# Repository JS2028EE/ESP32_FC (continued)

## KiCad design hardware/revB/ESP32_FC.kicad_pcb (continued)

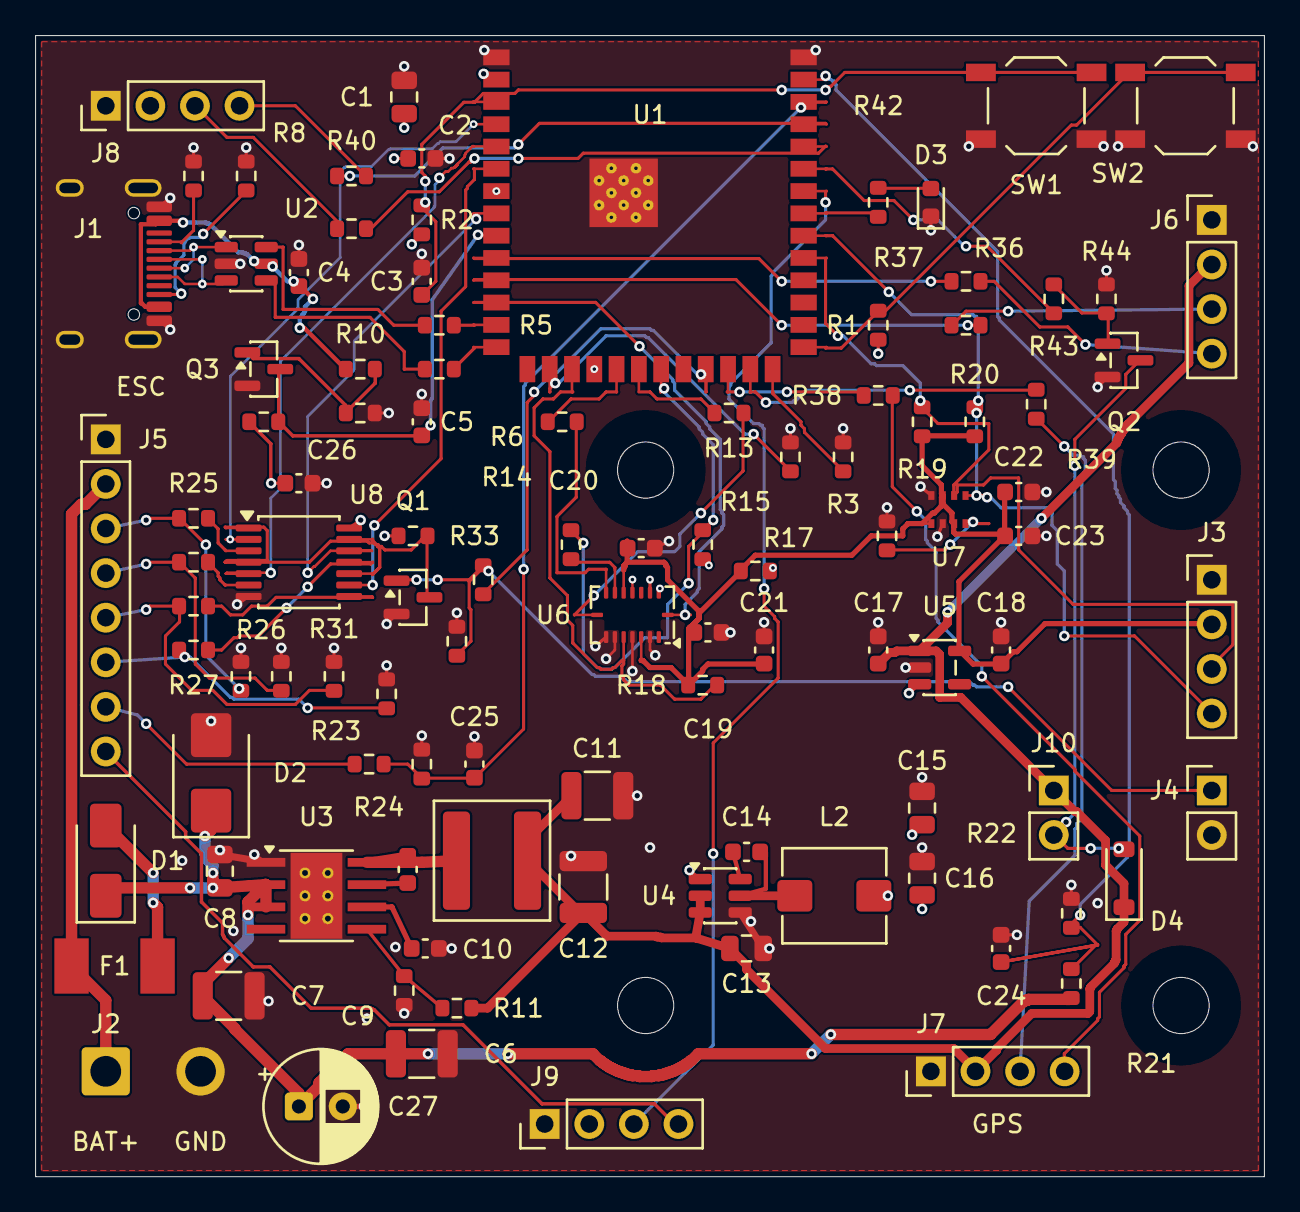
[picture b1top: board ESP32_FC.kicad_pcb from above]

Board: 4 copper layers, 70.0 x 65.0 mm, 107 parts (0 on the bottom side), 79 nets.

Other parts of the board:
H1, H2, H3, H4: MountingHole_3.2mm_M3

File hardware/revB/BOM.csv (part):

Reference,Value,MPN,Footprint,Specification,Sheet
C1,22u,GRM21BR61C226ME44L,Capacitor_SMD:C_0805_2012Metric,"X5R 16V 20%, 0805; board operation <=85C",ESP32_FC
C2,100n,GRM188R71C104KA01D,Capacitor_SMD:C_0603_1608Metric,"X7R, 16V",ESP32_FC
C3,1u,GRM188R71C105KA12D,Capacitor_SMD:C_0603_1608Metric,"X7R, 16V",ESP32_FC
C4,100n,GRM188R71C104KA01D,Capacitor_SMD:C_0603_1608Metric,"X7R, 16V",ESP32_FC
C5,10n,GRM188R71H103KA01D,Capacitor_SMD:C_0603_1608Metric,"X7R, 16V",ESP32_FC
J1,USB-C / USB2 FS,TYPE-C-31-M-12,FC_Prototype:USB_C_HRO_Edge,"['name', 'Specification']",ESP32_FC
Q3,DMN2056U,DMN2056U-7,Package_TO_SOT_SMD:SOT-23,VBUS detector; drain isolated from USB supply when MCU is unpowered,ESP32_FC
R1,10k,RC0603FR-0710KL,Resistor_SMD:R_0603_1608Metric,"1%, 0.1W",ESP32_FC
R2,10k,RC0603FR-0710KL,Resistor_SMD:R_0603_1608Metric,"1%, 0.1W",ESP32_FC
R3,10k,RC0603FR-0710KL,Resistor_SMD:R_0603_1608Metric,"1%, 0.1W",ESP32_FC
R4,10k,RC0603FR-0710KL,Resistor_SMD:R_0603_1608Metric,"1%, 0.1W",ESP32_FC
R5,22R,RC0603FR-0722RL,Resistor_SMD:R_0603_1608Metric,"1%, 0.1W",ESP32_FC
R6,22R,RC0603FR-0722RL,Resistor_SMD:R_0603_1608Metric,"1%, 0.1W",ESP32_FC
R7,5.1k,RC0603FR-075K1L,Resistor_SMD:R_0603_1608Metric,"1%, 0.1W",ESP32_FC
R8,5.1k,RC0603FR-075K1L,Resistor_SMD:R_0603_1608Metric,"1%, 0.1W",ESP32_FC
R9,10k,RC0603FR-0710KL,Resistor_SMD:R_0603_1608Metric,"1%, 0.1W",ESP32_FC
R10,100k,RC0603FR-07100KL,Resistor_SMD:R_0603_1608Metric,"1%, 0.1W",ESP32_FC
R46,10k,RC0603FR-0710KL,Resistor_SMD:R_0603_1608Metric,"1%, 0.1W; active-low VBUS sense pull-up",ESP32_FC
SW1,RESET,TL3342F160QG,Button_Switch_SMD:SW_SPST_TL3342,"['name', 'Specification']",ESP32_FC
SW2,BOOT,TL3342F160QG,Button_Switch_SMD:SW_SPST_TL3342,"['name', 'Specification']",ESP32_FC
U1,ESP32-S3-WROOM-1-N8R8,ESP32-S3-WROOM-1-N8R8,FC_Prototype:ESP32_S3_WROOM_Edge,8MB flash / 8MB octal PSRAM; GPIO35/36/37 unavailable,ESP32_FC
U2,USBLC6-2SC6,USBLC6-2SC6,Package_TO_SOT_SMD:SOT-23-6,"['name', 'Specification']",ESP32_FC
C6,2.2u / 100V,GRM32ER72A225KA35L,Capacitor_SMD:C_1210_3225Metric,Murata 1210 X7R 100V 10%; ceramic bypass plus C27 bulk damping,Power
C7,2.2u / 100V,GRM32ER72A225KA35L,Capacitor_SMD:C_1210_3225Metric,Murata 1210 X7R 100V 10%; local input bypass,Power
C8,220n / 100V,C0805C224K1RACTU,Capacitor_SMD:C_0805_2012Metric,X7R 100V directly at VIN-PGND,Power
C9,1u / 16V,GRM188R71C105KA12D,Capacitor_SMD:C_0603_1608Metric,"X7R, 16V",Power
C10,100n,GRM188R71C104KA01D,Capacitor_SMD:C_0603_1608Metric,"X7R, 16V",Power
C11,22u / 25V,GRM32ER71E226KE15L,Capacitor_SMD:C_1210_3225Metric,"X7R 25V 10%, 1210; both output capacitors required; DC-bias/temperature derating applies",Power
C12,22u / 25V,GRM32ER71E226KE15L,Capacitor_SMD:C_1210_3225Metric,"X7R 25V 10%, 1210; both output capacitors required; DC-bias/temperature derating applies",Power
C13,22u,GRM21BR61C226ME44L,Capacitor_SMD:C_0805_2012Metric,"X5R 16V 20%, 0805; input capacitor; operating board temperature <=85C",Power
C14,100n,GRM188R71C104KA01D,Capacitor_SMD:C_0603_1608Metric,"X7R, 16V",Power
C15,22u,GRM21BR61C226ME44L,Capacitor_SMD:C_0805_2012Metric,"X5R 16V 20%, 0805; board operation <=85C",Power
C16,22u,GRM21BR61C226ME44L,Capacitor_SMD:C_0805_2012Metric,"X5R 16V 20%, 0805; board operation <=85C",Power
C17,1u,GRM188R71C105KA12D,Capacitor_SMD:C_0603_1608Metric,"X7R, 16V",Power
C18,4.7u,GRM188R61C475KE11D,Capacitor_SMD:C_0603_1608Metric,"X5R 16V 10%, 0603; board operation <=85C",Power
C27,47u / 50V,EEUFR1H470,Capacitor_THT:CP_Radial_D6.3mm_P2.50mm,"Panasonic FR; D6.3mm, H11.2mm, P2.5mm; polarized input damping capacitor",Power
D1,SS310 / 100V 3A,SS310-13-F,Diode_SMD:D_SMA,"SMA variant; anode toward battery, cathode toward protected input",Power
D2,SMBJ28A,SMBJ28A-13-F,Diode_SMD:D_SMB,Unidirectional TVS; 28V standoff; cathode VIN_PROT. Zener-style symbol denotes avalanche TVS.,Power
F1,1A / 476,0476001.MR,FC_Prototype:Fuse_Littelfuse_476,"Littelfuse 476, 1A fast; 10kA at 86VDC; 2410 package. FC branch only.",Power
J2,BATTERY 3S-6S,WIRE CONNECTION - NO FITTED PART,Connector_Wire:SolderWire-1sqmm_1x02_P5.4mm_D1.4mm_OD2.7mm,Low-current FC supply only. Motor current does not flow through this board.,Power
L1,22uH,SRP6060FA-220M,Inductor_SMD:L_Bourns_SRP6060FA,"22uH; 5.6A typical saturation, 3.8A RMS at 20C rise; 60.5mOhm max DCR",Power
L2,4.7uH,SRP5030T-4R7M,Inductor_SMD:L_Bourns_SRP5030T,"4.7uH; 6A typical saturation, 4.6A RMS; 53mOhm max DCR; AP63203 allowed 2.2-10uH range",Power
R11,80.6k,RC0603FR-0780K6L,Resistor_SMD:R_0603_1608Metric,"1%, 0.1W",Power
R12,20k,RC0603FR-0720KL,Resistor_SMD:R_0603_1608Metric,"1%, 0.1W",Power
U3,LMR36510ADDAR,LMR36510ADDAR,Package_SO:Texas_HTSOP-8-1EP_3.9x4.9mm_P1.27mm_EP2.95x4.9mm_Mask2.4x3.1mm_ThermalVias,"65V rated input, 1A output, 400kHz; exposed pad to GND",Power
U4,AP63203WU-7,AP63203WU-7,Package_TO_SOT_SMD:TSOT-23-6,Fixed 3.3V synchronous buck; upstream 5V stage limits total power,Power
U5,TLV75533PDBVR,TLV75533PDBVR,Package_TO_SOT_SMD:SOT-23-5,Sensor-only supply; EN from digital 3V3 sequences sensors after MCU rail,Power
C19,100n,GRM188R71C104KA01D,Capacitor_SMD:C_0603_1608Metric,Place at BMI088 pin3 VDD,Sensors
C20,100n,GRM188R71C104KA01D,Capacitor_SMD:C_0603_1608Metric,Place at BMI088 pin11 VDDIO,Sensors
C21,4.7u,GRM188R61C475KE11D,Capacitor_SMD:C_0603_1608Metric,"X5R 16V 10%, 0603; board operation <=85C",Sensors
C22,100n,GRM188R71C104KA01D,Capacitor_SMD:C_0603_1608Metric,At BMP280 VDD,Sensors
C23,100n,GRM188R71C104KA01D,Capacitor_SMD:C_0603_1608Metric,At BMP280 VDDIO,Sensors
C24,100n,GRM188R71C104KA01D,Capacitor_SMD:C_0603_1608Metric,"X7R, 16V",Sensors
C25,100n,GRM188R71C104KA01D,Capacitor_SMD:C_0603_1608Metric,"X7R, 16V",Sensors
J3,I2C / 3.3V ONLY,TSW-104-07-G-S,Connector_PinHeader_2.54mm:PinHeader_1x04_P2.54mm_Vertical,Pinout defined by this schematic; verify mating cable,Sensors
R13,33R,RC0603FR-0733RL,Resistor_SMD:R_0603_1608Metric,"1%, 0.1W",Sensors
R14,33R,RC0603FR-0733RL,Resistor_SMD:R_0603_1608Metric,"1%, 0.1W",Sensors
R15,33R,RC0603FR-0733RL,Resistor_SMD:R_0603_1608Metric,"1%, 0.1W",Sensors
R16,33R,RC0603FR-0733RL,Resistor_SMD:R_0603_1608Metric,"1%, 0.1W",Sensors
R17,10k,RC0603FR-0710KL,Resistor_SMD:R_0603_1608Metric,"1%, 0.1W",Sensors
R18,10k,RC0603FR-0710KL,Resistor_SMD:R_0603_1608Metric,"1%, 0.1W",Sensors
R19,4.7k,RC0603FR-074K7L,Resistor_SMD:R_0603_1608Metric,"1%, 0.1W",Sensors
R20,4.7k,RC0603FR-074K7L,Resistor_SMD:R_0603_1608Metric,"1%, 0.1W",Sensors
R21,150k,RT0603BRD07150KL,Resistor_SMD:R_0603_1608Metric,"0.1%, 0.1W; >=50V working voltage; protected voltage sense after reverse diode",Sensors
R22,10k,RT0603BRD0710KL,Resistor_SMD:R_0603_1608Metric,"0.1%, 0.1W",Sensors
R23,10k,RC0603FR-0710KL,Resistor_SMD:R_0603_1608Metric,"1%, 0.1W",Sensors
R24,10k,RC0603FR-0710KL,Resistor_SMD:R_0603_1608Metric,"1%, 0.1W",Sensors
R45,10k,RC0603FR-0710KL,Resistor_SMD:R_0603_1608Metric,"1%, 0.1W",Sensors
U6,BMI088,BMI088,Package_LGA:Bosch_LGA-16_4.5x3mm_P0.5mm_LayoutBorder7x1y_ClockwisePinNumbering,PS low selects gyro SPI; CS1 accel / CS2 gyro; 10MHz SPI maximum,Sensors
U7,BMP280,BMP280,FC_Prototype:BMP280_SilkClear,"I2C address 0x76. Pressure sensor, not a compass.",Sensors
C26,100n,GRM188R71C104KA01D,Capacitor_SMD:C_0603_1608Metric,"X7R, 16V",Interfaces
J4,KILL STRAP,TSW-102-07-G-S,Connector_PinHeader_2.54mm:PinHeader_1x02_P2.54mm_Vertical,"Short these pins to force outputs disabled, including when GPIO21 is high",Interfaces
J5,4-IN-1 ESC,TSW-108-07-G-S,Connector_PinHeader_2.54mm:PinHeader_1x08_P2.54mm_Vertical,Pinout defined by this schematic; verify mating cable,Interfaces
J6,CRSF RECEIVER,TSW-104-07-G-S,Connector_PinHeader_2.54mm:PinHeader_1x04_P2.54mm_Vertical,Pinout defined by this schematic; verify mating cable,Interfaces
J7,GPS UART,TSW-104-07-G-S,Connector_PinHeader_2.54mm:PinHeader_1x04_P2.54mm_Vertical,Pinout defined by this schematic; verify mating cable,Interfaces
Q1,DMN2056U,DMN2056U-7,Package_TO_SOT_SMD:SOT-23,GPIO21 HIGH enables motor buffers; pull-down disables on MCU reset,Interfaces
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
